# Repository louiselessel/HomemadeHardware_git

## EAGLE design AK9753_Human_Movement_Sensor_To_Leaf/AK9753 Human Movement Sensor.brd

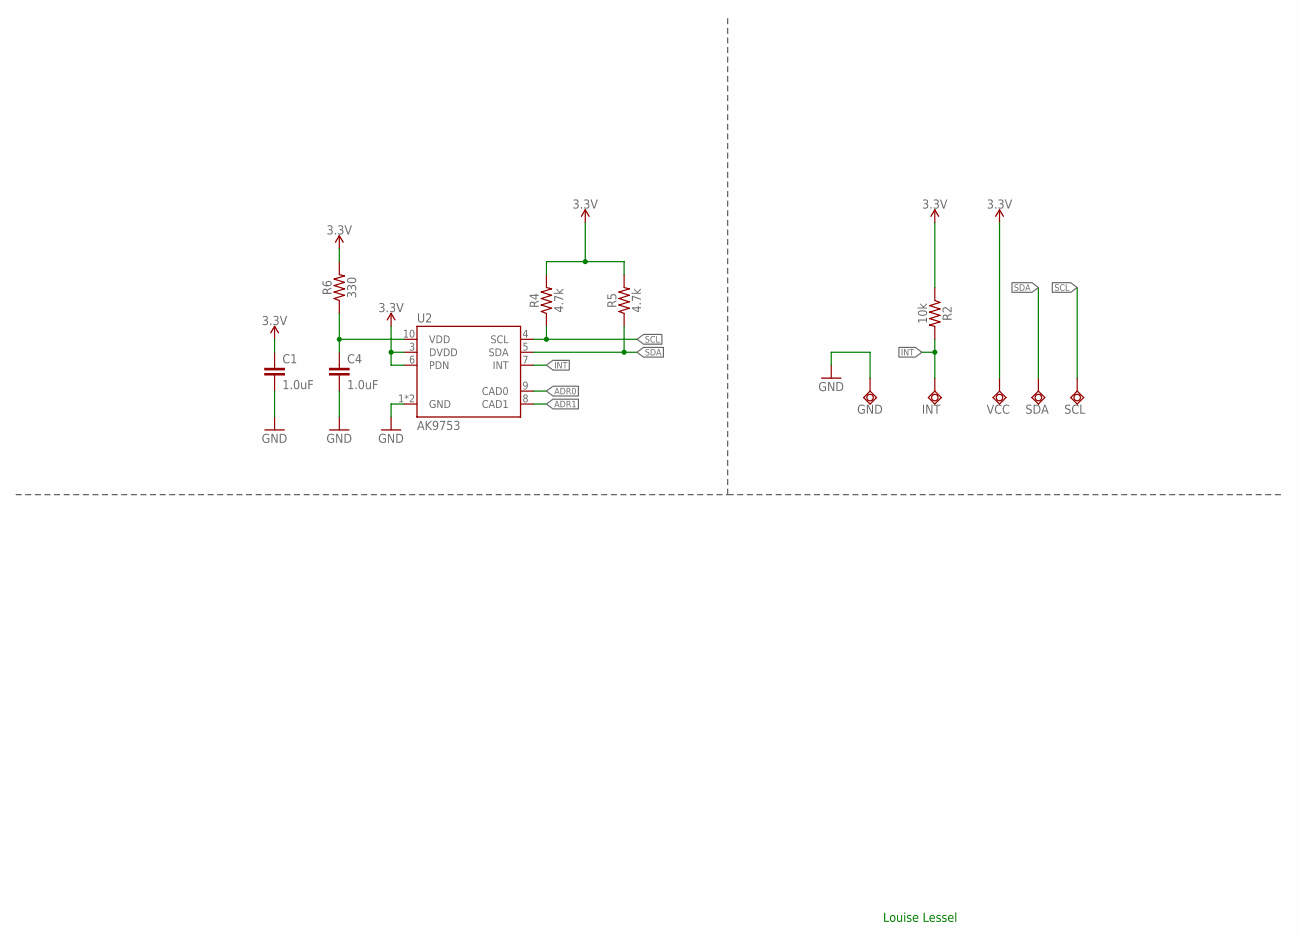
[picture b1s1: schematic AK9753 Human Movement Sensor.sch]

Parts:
C1, C4: 1.0uF; 0603
GND: TPSQTP20R; TP20R
INT: TPSQTP20R; TP20R
R2: 10k; 0603
R4, R5: 4.7k; 0603
R6: 330; 0603
SCL: TPSQTP20R; TP20R
SDA: TPSQTP20R; TP20R
U2: AK9753; SON10
VCC: TPSQTP20R; TP20R

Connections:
3.3V: C1.1, R2.1, R4.2, R5.2, R6.2, U2.3 (DVDD), U2.6 (PDN), VCC.TP
!INT: INT.TP, R2.2, U2.7 (INT)
ADR0: U2.9 (CAD0)
ADR1: U2.8 (CAD1)
GND: C1.2, C4.2, GND.TP, U2.1 (GND), U2.2 (GND)
SCL: R4.1, SCL.TP, U2.4 (SCL)
SDA: R5.1, SDA.TP, U2.5 (SDA)
VDD: C4.1, R6.1, U2.10 (VDD)

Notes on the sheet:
Louise Lessel

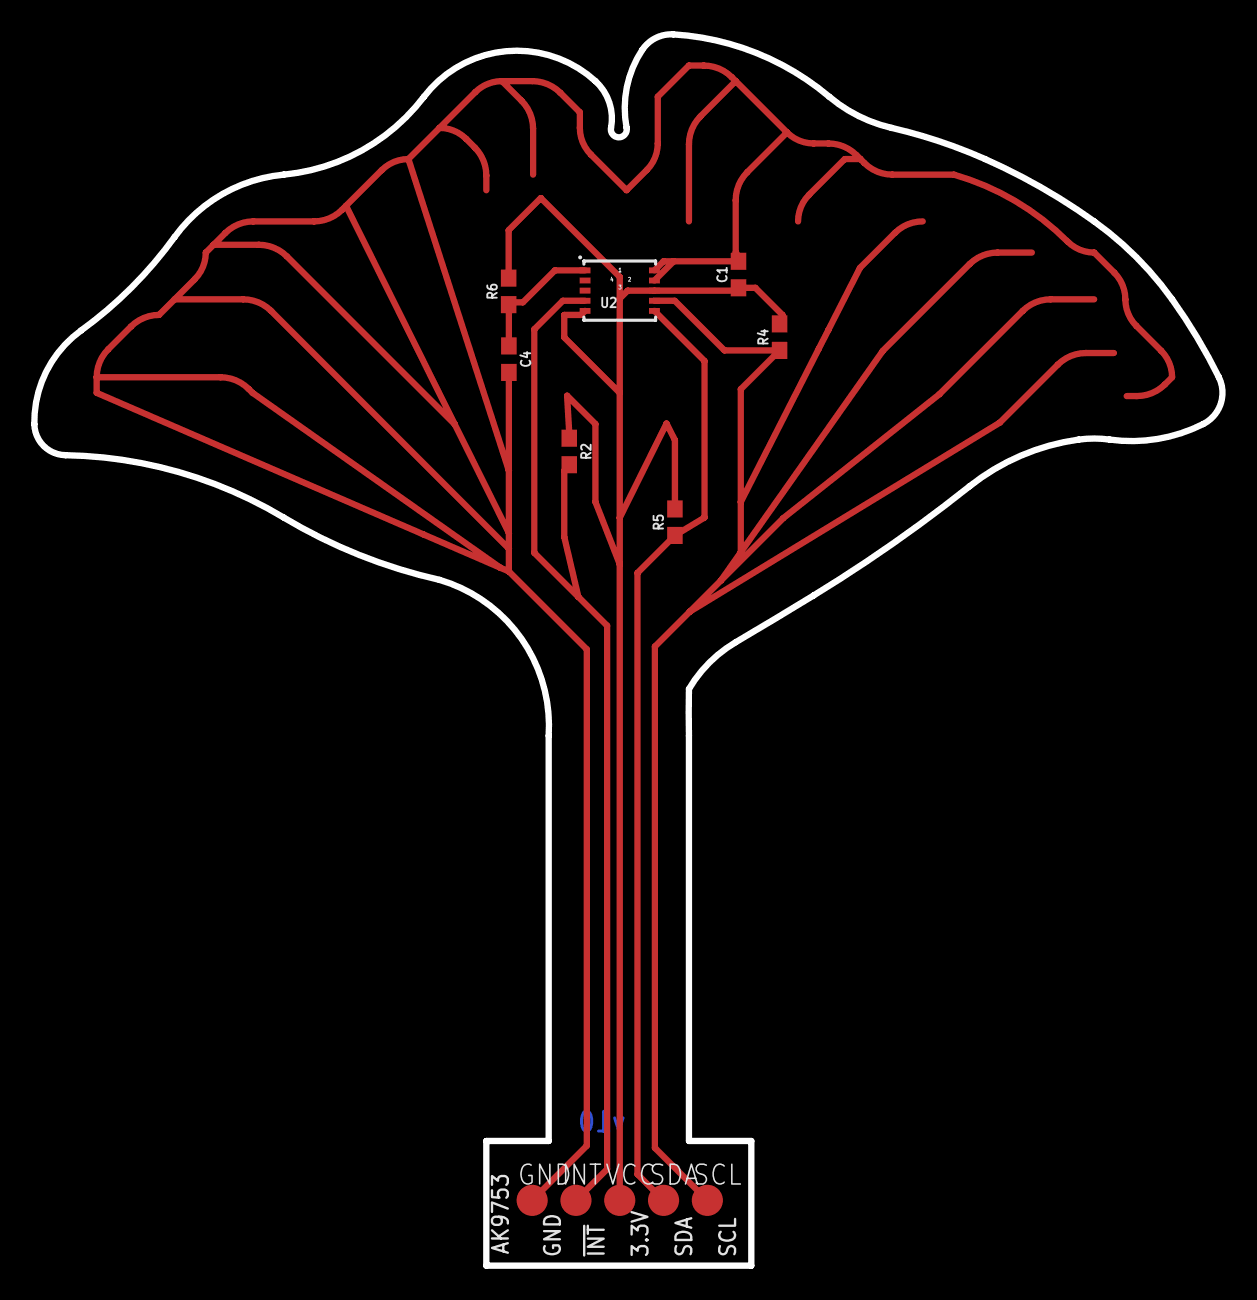
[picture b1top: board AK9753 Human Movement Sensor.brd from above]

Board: 2 copper layers, 76.2 x 79.0 mm, 12 parts (0 on the bottom side), 6 nets.

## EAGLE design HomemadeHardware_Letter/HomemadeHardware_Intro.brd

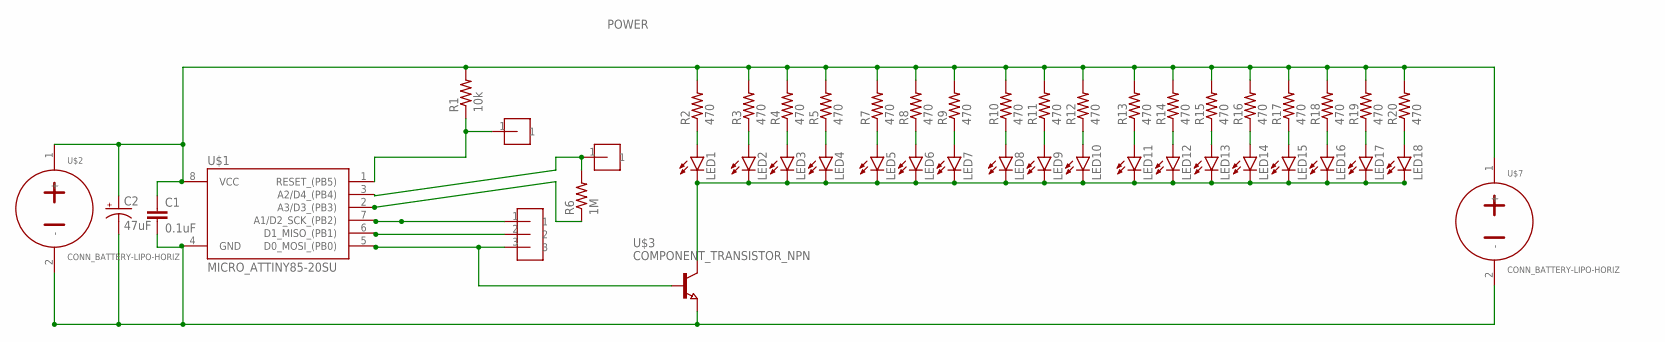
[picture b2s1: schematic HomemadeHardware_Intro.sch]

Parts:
C1: 0.1uF; 0805
C2: 47uF; CAP_RADIAL_CAN_8MM
LED1, LED2, LED3, LED4, LED5, LED6, LED7, LED8, LED9, LED10, LED11, LED12, LED13, LED14, LED15, LED16, LED17, LED18: LED-0805; CHIP-LED0805
R1: 10k; 0805
R2, R3, R4, R5, R7, R8, R9, R10, R11, R12, R13, R14, R15, R16, R17, R18, R19, R20: 470; 0805
R6: 1M; 0805
U$1: MICRO_ATTINY85-20SU; SOIC8
U$2, U$7: CONN_BATTERY-LIPO-HORIZ; JST-PH-2-SMT-RA
U$3: COMPONENT_TRANSISTOR_NPN; SOT23
U$4, U$5: HEADER-1-TESTPOINT; TESTPOINT-1
U$6: HEADER-3-TESTPOINT; TESTPOINT-3

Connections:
unnamed: R1.1, U$1.1 (RESET_(PB5)), U$5.1
unnamed: C1.2, C2.-, U$1.4 (GND), U$2.2 (-), U$3.2 (E), U$7.2 (-)
unnamed: LED14.A, R16.1
unnamed: R6.2, U$1.3 (A2/D4_(PB4)), U$4.1
unnamed: LED1.C, LED2.C, LED3.C, LED4.C, LED5.C, LED6.C, LED7.C, LED8.C, LED9.C, LED10.C, LED11.C, LED12.C, LED13.C, LED14.C, LED15.C, LED16.C, LED17.C, LED18.C, U$3.3 (C)
unnamed: LED4.A, R5.1
unnamed: LED3.A, R4.1
unnamed: LED2.A, R3.1
unnamed: LED1.A, R2.1
unnamed: R6.1, U$1.2 (A3/D3_(PB3))
unnamed: U$1.5 (D0_MOSI_(PB0)), U$3.1 (B), U$6.3
unnamed: U$1.7 (A1/D2_SCK_(PB2)), U$6.1
unnamed: U$1.6 (D1_MISO_(PB1)), U$6.2
unnamed: LED7.A, R9.1
unnamed: LED6.A, R8.1
unnamed: LED5.A, R7.1
unnamed: LED15.A, R17.1
unnamed: LED10.A, R12.1
unnamed: LED9.A, R11.1
unnamed: LED8.A, R10.1
unnamed: LED16.A, R18.1
unnamed: LED13.A, R15.1
unnamed: LED12.A, R14.1
unnamed: LED11.A, R13.1
unnamed: LED17.A, R19.1
unnamed: LED18.A, R20.1
POWER: C1.1, C2.+, R1.2, R2.2, R3.2, R4.2, R5.2, R7.2, R8.2, R9.2, R10.2, R11.2, R12.2, R13.2, R14.2, R15.2, R16.2, R17.2, R18.2, R19.2, R20.2, U$1.8 (VCC), U$2.1 (+), U$7.1 (+)

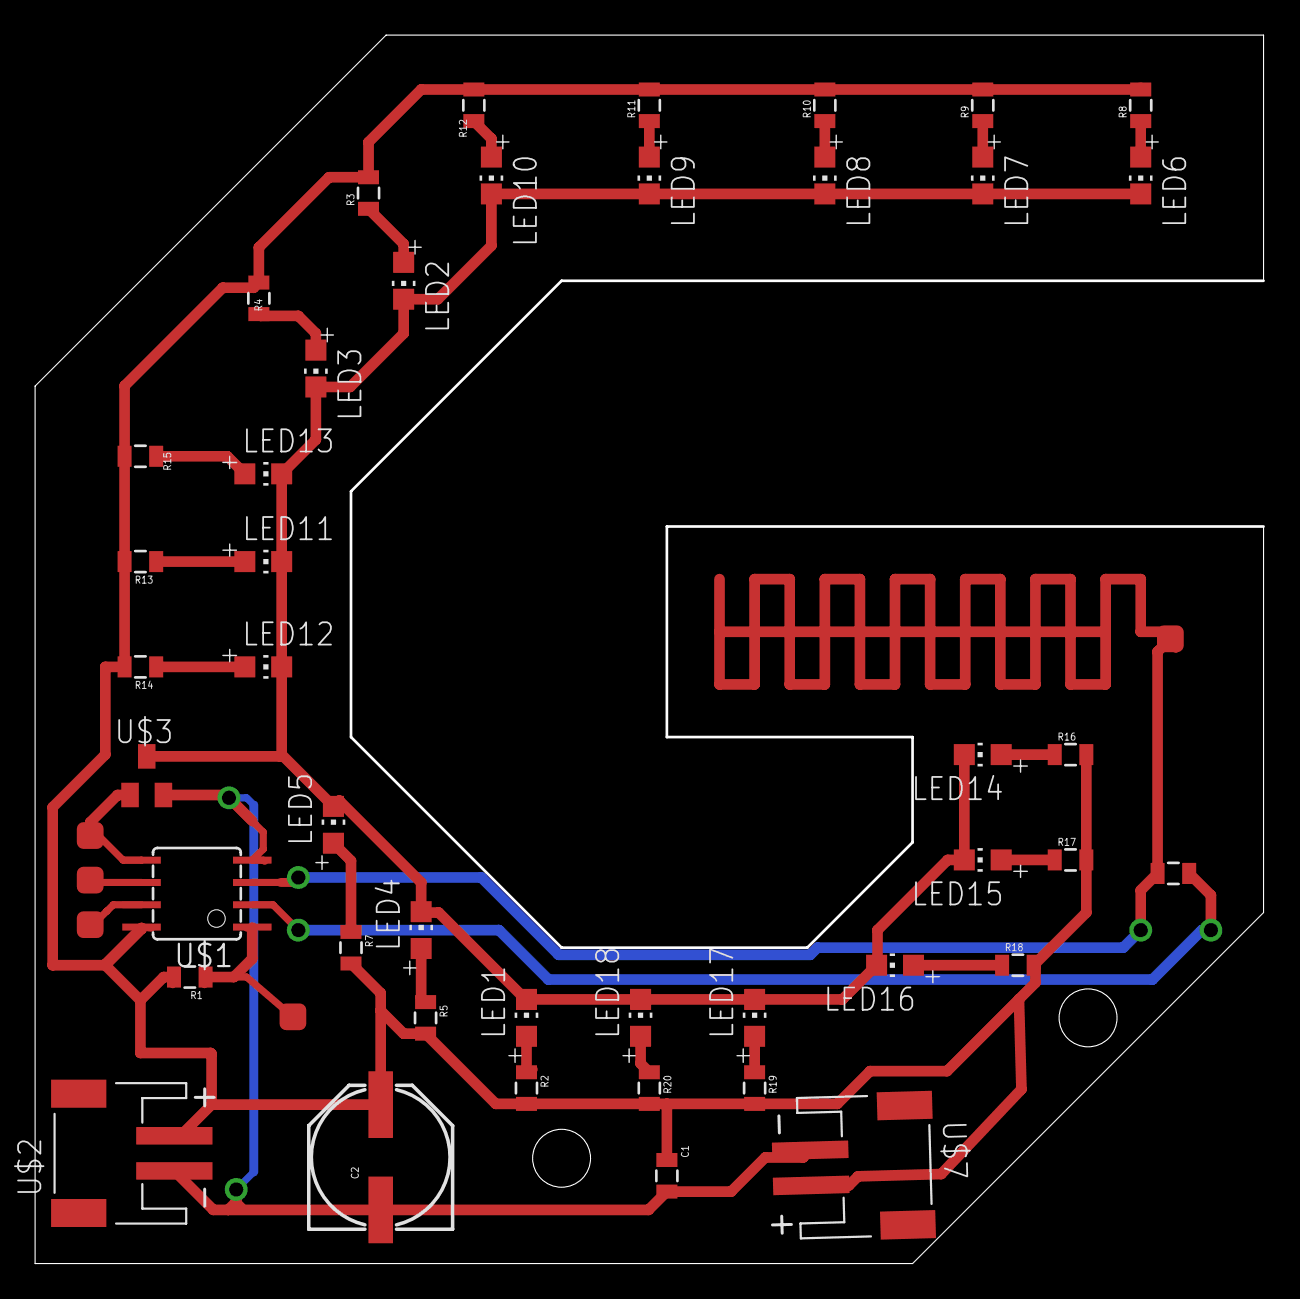
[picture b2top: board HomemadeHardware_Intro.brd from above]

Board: 2 copper layers, 70.0 x 70.0 mm, 47 parts (0 on the bottom side), 27 nets.

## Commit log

2020-02-21 Added initial board test
    Still need to make capacitive sensor
2020-02-21 renamed to letter assignment
2020-02-21 pdf added
2020-02-21 made on board capacitive sensor
2020-02-26 fixed before pcb prunt. made some carves smaller
2020-03-27 pdfs
2020-04-17 Human Presence Sensor Project
2020-04-24 Finished schematic
    drawing board next
2020-04-24 Leaf outline done
2020-04-24 Leaf structure done
2020-04-24 small changes

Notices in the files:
parts and their libraries:
SparkFun-Resistors: Licensing: Creative Commons ShareAlike 4.0 International - https://creativecommons.org/licenses/by-sa/4.0
